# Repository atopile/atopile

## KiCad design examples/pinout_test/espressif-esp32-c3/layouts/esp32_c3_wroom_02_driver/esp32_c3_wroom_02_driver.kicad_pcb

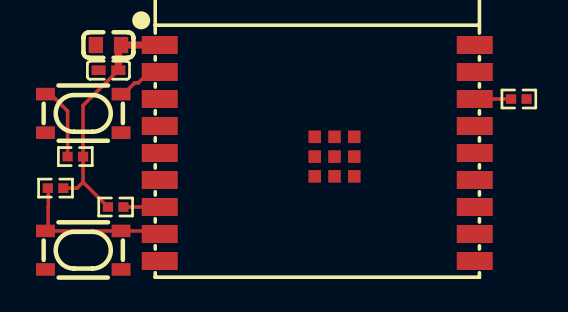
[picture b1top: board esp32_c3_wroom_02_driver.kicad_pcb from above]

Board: 2 copper layers, 9 parts (0 on the bottom side), 6 nets.

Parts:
C3: 22µF ±20% 6.3V X5R; C0603
C4: 100nF ±10% 16V X7R; C0402
R1, R2, R3: 10kΩ ±1% 62.5mW; R0402
R4: 5.1kΩ ±1% 62.5mW; R0402
SW1, SW2: KEY-SMD_4P-L4.2-W3.2-P2.20-LS4.6
U1: WIFIM-SMD_18P-L20.0-W18.0-P1.50

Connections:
GND: C3.2, C4.2, SW1.1, SW1.2, SW2.1, SW2.2, U1.9, U1.19
MISO: R2.1, U1.7
N_TRST: R3.2, SW2.3, SW2.4, U1.2
VCC: C3.1, C4.1, R1.2, R2.2, R3.1, R4.1, U1.1
data_1: R1.1, U1.16
output: R4.2, SW1.3, SW1.4, U1.8

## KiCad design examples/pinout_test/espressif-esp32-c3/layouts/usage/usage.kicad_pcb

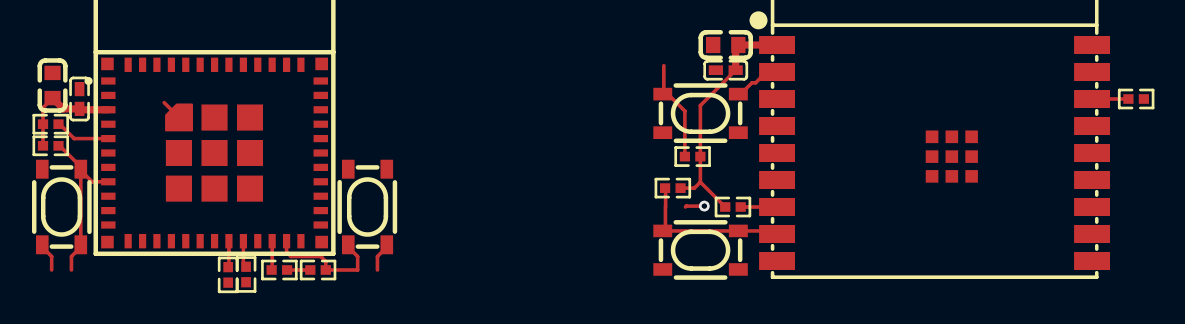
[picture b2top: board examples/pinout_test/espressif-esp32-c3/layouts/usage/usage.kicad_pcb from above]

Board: 2 copper layers, 20 parts (0 on the bottom side), 16 nets.

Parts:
C2, C6: 22µF ±20% 6.3V X5R; C0603
C3, C7: 100nF ±10% 16V X7R; C0402
R1, R2, R4, R5, R6, R7, R8, R10: 10kΩ ±1% 62.5mW; R0402
R3, R9: 5.1kΩ ±1% 62.5mW; R0402
SW1, SW2, SW3, SW4: KEY-SMD_4P-L4.2-W3.2-P2.20-LS4.6
U1: WIFIM-SMD_ESP32-C3-MINI-1
U2: WIFIM-SMD_18P-L20.0-W18.0-P1.50

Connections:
GND: C2.2, C3.2, C6.2, C7.2, SW1.1, SW1.2, SW2.1, SW2.2, SW3.1, SW3.2, SW4.1, SW4.2, U1.1, U1.2, U1.11, U1.14, U1.36, U1.37, U1.38, U1.39, U1.40, U1.41, U1.42, U1.43, U1.44, U1.45, U1.46, U1.47, U1.48, U1.49, U1.50, U1.51, U1.52, U1.53, U2.9, U2.19
MISO: R2.1, R8.1, U1.22, U2.7
MOSI: U1.21, U2.6
SCK: U1.12, U2.18
SCL: R6.2, U1.20, U2.5
SCLK: U1.16, U2.10
SD: U1.13, U2.17
SDA: R5.2, U1.19, U2.4
VCC: C2.1, C3.1, C6.1, C7.1, R1.2, R2.2, R3.1, R4.1, R5.1, R6.1, R7.2, R8.2, R9.1, R10.1, U1.3, U2.1
WS: U1.6, U2.15
mini_module-gpio[9]-output: R3.2, SW1.3, SW1.4, U1.23
mini_module-jtag-N_TRST: R4.2, SW2.3, SW2.4, U1.8
mini_module-mspi[2]-data_1: R1.1, U1.5
wroom_module-gpio[9]-output: R9.2, SW3.3, SW3.4, U2.8
wroom_module-jtag-N_TRST: R10.2, SW4.3, SW4.4, U2.2
wroom_module-mspi[2]-data_1: R7.1, U2.16

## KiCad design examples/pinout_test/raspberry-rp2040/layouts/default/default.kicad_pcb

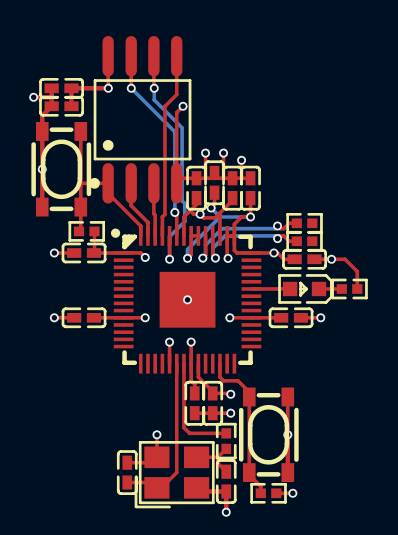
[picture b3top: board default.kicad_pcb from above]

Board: 4 copper layers, 26 parts (0 on the bottom side), 17 nets.

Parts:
C2, C8, C15: 2.2µF ±20% 6.3V X5R; C0402
C3, C4, C9, C10, C11, C12, C13, C14, C16: 100nF ±10% 16V X7R; C0402
C5, C6: 15pF ±5% 50V C0G; C0402
LED1: LED0603-RD
R1, R3, R4: 10kΩ ±1% 62.5mW; R0402
R2: 1kΩ ±1% 62.5mW; R0402
R5, R6: 27Ω ±1% 62.5mW; R0402
SW1, SW2: KEY-SMD_4P-L4.2-W3.2-P2.20-LS4.6
U1: LQFN-56_L7.0-W7.0-P0.4-EP
U2: SOIC-8_L5.3-W5.3-P1.27-LS8.0-BL
X1: CRYSTAL-SMD_4P-L3.2-W2.5-BL

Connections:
A: LED1.2, U1.37
GND: C2.2, C3.2, C4.2, C5.2, C6.2, C8.2, C9.2, C10.2, C11.2, C12.2, C13.2, C14.2, C15.2, C16.2, R3.1, SW1.3, SW1.4, SW2.3, SW2.4, U1.19, U1.57, U2.4, X1.2, X1.4
K: LED1.1, R3.2
RUN: R4.1, SW2.1, SW2.2, U1.26
XIN: C5.1, U1.20, X1.1
XOUT: R2.2, U1.21
_core_regulator_out_power-VCC: C2.1, C3.1, C4.1, U1.23, U1.45, U1.50
chip_select: R1.1, SW1.1, SW1.2, U1.56, U2.1
clock: U1.52, U2.6
data_0: U1.53, U2.5
data_1: U1.55, U2.2
data_2: U1.54, U2.3
data_3: U1.51, U2.7
output: C6.1, R2.1, X1.3
output-USB_D_N: R6.2, U1.46
output-USB_D_P: R5.2, U1.47
power-VCC: C8.1, C9.1, C10.1, C11.1, C12.1, C13.1, C14.1, C15.1, C16.1, R1.2, R4.2, U1.1, U1.10, U1.22, U1.33, U1.42, U1.43, U1.44, U1.48, U1.49, U2.8

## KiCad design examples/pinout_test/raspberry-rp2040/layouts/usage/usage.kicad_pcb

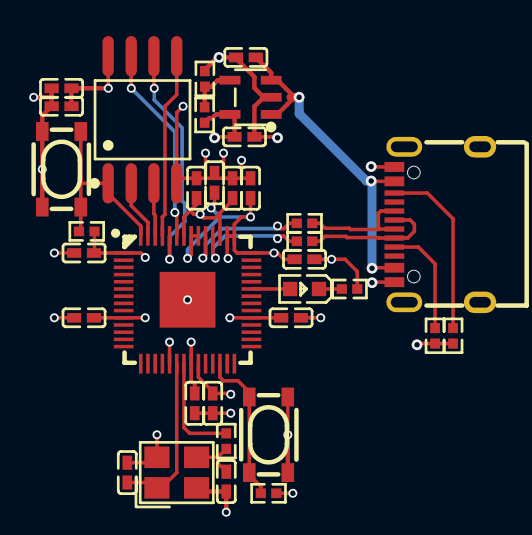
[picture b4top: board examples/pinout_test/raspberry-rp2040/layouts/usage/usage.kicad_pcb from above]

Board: 4 copper layers, 34 parts (0 on the bottom side), 23 nets.

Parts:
C1, C2: 1µF ±10% 25V X5R; C0402
C4, C9, C16: 2.2µF ±20% 6.3V X5R; C0402
C5, C6, C10, C11, C12, C13, C14, C15, C17: 100nF ±10% 16V X7R; C0402
C7, C8: 15pF ±5% 50V C0G; C0402
LED1: LED0603-RD
R1, R3, R5, R6: 10kΩ ±1% 62.5mW; R0402
R2: 20kΩ ±1% 62.5mW; R0402
R4: 1kΩ ±1% 62.5mW; R0402
R7, R8: 27Ω ±1% 62.5mW; R0402
R9, R10: 51kΩ ±1% 62.5mW; R0402
SW1, SW2: KEY-SMD_4P-L4.2-W3.2-P2.20-LS4.6
U1: SOT-23-5_L3.0-W1.7-P0.95-LS2.8-BL
U2: LQFN-56_L7.0-W7.0-P0.4-EP
U3: SOIC-8_L5.3-W5.3-P1.27-LS8.0-BL
USB1: USB-C-SMD_TYPE-C-6PIN-2MD-073
X1: CRYSTAL-SMD_4P-L3.2-W2.5-BL

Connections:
A: LED1.2, U2.37
CC1: R9.2, USB1.4
CC2: R10.2, USB1.10
GND: C1.2, C2.2, C4.2, C5.2, C6.2, C7.2, C8.2, C9.2, C10.2, C11.2, C12.2, C13.2, C14.2, C15.2, C16.2, C17.2, R1.2, R5.1, R9.1, R10.1, SW1.3, SW1.4, SW2.3, SW2.4, U1.2, U2.19, U2.57, U3.4, USB1.1, USB1.12, USB1.13, USB1.14, X1.2, X1.4
K: LED1.1, R5.2
RUN: R6.1, SW2.1, SW2.2, U2.26
VDIV_OUTPUT: R1.1, R2.2, U1.4
XIN: C7.1, U2.20, X1.1
XOUT: R4.2, U2.21
_core_regulator_out_power-VCC: C4.1, C5.1, C6.1, U2.23, U2.45, U2.50
chip_select: R3.1, SW1.1, SW1.2, U2.56, U3.1
clock: U2.52, U3.6
data_0: U2.53, U3.5
data_1: U2.55, U3.2
data_2: U2.54, U3.3
data_3: U2.51, U3.7
input-USB_D_N: R8.1, USB1.5, USB1.7
input-USB_D_P: R7.1, USB1.6, USB1.8
output: C8.1, R4.1, X1.3
output-USB_D_N: R8.2, U2.46
output-USB_D_P: R7.2, U2.47
power-VCC: C2.1, C9.1, C10.1, C11.1, C12.1, C13.1, C14.1, C15.1, C16.1, C17.1, R2.1, R3.2, R6.2, U1.5, U2.1, U2.10, U2.22, U2.33, U2.42, U2.43, U2.44, U2.48, U2.49, U3.8
power_in-VCC: C1.1, U1.1, U1.3, USB1.2, USB1.11

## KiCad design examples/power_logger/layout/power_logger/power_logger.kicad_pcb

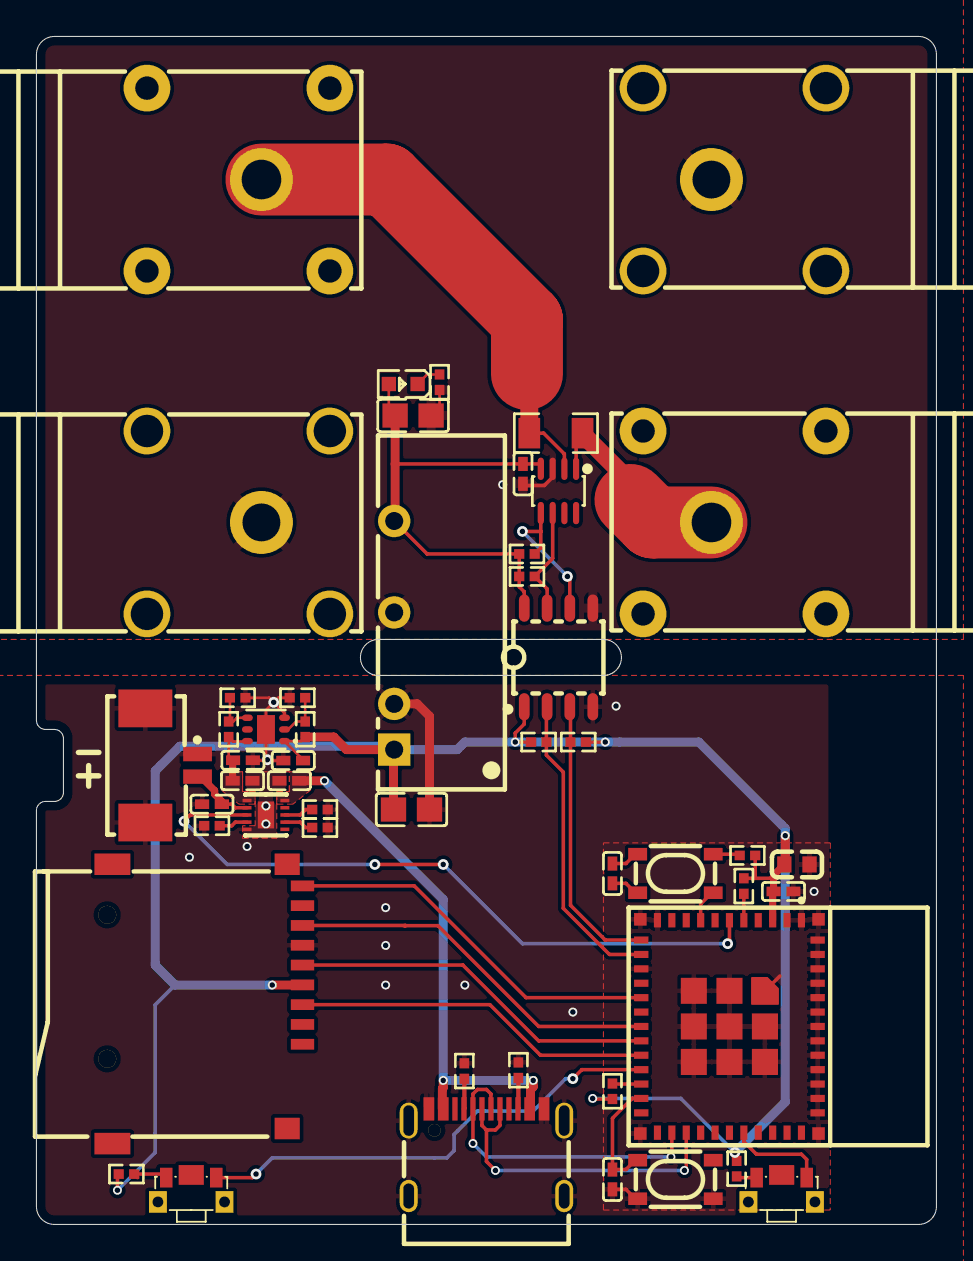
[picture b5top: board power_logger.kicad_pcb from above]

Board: 2 copper layers, 50.0 x 66.0 mm, 51 parts (1 on the bottom side), 38 nets.

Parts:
B1: EEMB_BATTERY_LP402535
C1, C3, C5, C6: 1µF ±10% 25V X5R; C0402
C2: 10µF ±20% 6.3V X5R; C0402
C4, C7, C8, C12: 100nF ±10% 16V X7R; C0402
C9: 22µF ±20% 6.3V X5R; C0603
C10: 2.2µF ±10% 25V X7R; C0805
C11: 10µF ±10% 25V X5R; C0805
Card1: TF-SMD_TF-01A
D1: LED0603-RD
J1, J3: ANT-TH_L33.0-W12.0_BLACK
J2, J4: ANT-TH_L33.0-W12.0_RED
R1, R2, R4, R5, R10, R11, R12, R13, R14, R15, R19, R20: 10kΩ ±1% 62.5mW; R0402
R3, R7: 100kΩ ±1% 62.5mW; R0402
R6: 25mΩ ±1% 1W; R1206
R8: 150kΩ ±1% 62.5mW; R0402
R9, R18: 2kΩ ±1% 62.5mW; R0402
R16, R17: 4.7kΩ ±1% 62.5mW; R0402
SW1, SW2: KEY-SMD_SKTDLDE010
SW3, SW4: KEY-SMD_4P-L4.2-W3.2-P2.20-LS4.6
U1: WSON-10_L2.2-W2.0-P0.40-BL-EP_TI_DLH0010A
U2: SOT-23-8_L2.9-W1.6-P0.65-LS2.8-BR
U3: WSON-6_L2.0-W2.0-P0.65-TL-EP
U4: WIFIM-SMD_ESP32-C3-MINI-1
U5: PWRM-TH_BXXXXS-2WR3
U6: SOIC-8_L4.9-W3.9-P1.27-LS6.0-TL
U7: CONN-SMD_532610271
USB1: USB-C-SMD_KH-TYPE-C-16P

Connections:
A5: R16.1, USB1.A5
B5: R17.1, USB1.B5
CD: Card1.9, U4.16
EN: R7.1, R8.2, U3.4
FB: R9.1, R10.2, U3.2
GND: Card1.10, Card1.11, Card1.12, Card1.13
ILIM_VSET: R3.1, U1.7
INneg: J4.5, R6.2, U2.2
INpos: J2.5, R6.1, U2.1
ISET: R1.1, U1.8
SCL2: R19.1, U2.5, U6.6
SDA2: R20.1, U2.6, U6.7
cathode: D1.1, R18.1
gnd: C1.2, C2.2, C3.2, C5.2, C6.2, C7.1, C9.2, C10.2, C12.2, Card1.6, R1.2, R2.2, R3.2, R7.2, R9.2, R16.2, R17.2, SW3.1, SW3.2, U1.5, U1.11, U3.3, U3.7, U4.1, U4.2, U4.11, U4.14, U4.36, U4.37, U4.38, U4.39, U4.40, U4.41, U4.42, U4.43, U4.44, U4.45, U4.46, U4.47, U4.48, U4.49, U4.50, U4.51, U4.52, U4.53, U5.2, U6.4, U7.1, U7.3, U7.4, USB1.1, USB1.2, USB1.3, USB1.4, USB1.A1, USB1.A12, USB1.B1, USB1.B12
gnd-1: C4.2, C11.2, J1.5, J3.5, R18.2, U2.3, U2.7, U5.4, U6.5
hv: C5.1, C9.1, C10.1, C12.1, Card1.4, R4.2, R5.2, R10.1, R11.2, R12.2, R13.2, R14.2, R15.2, U3.1, U4.3, U5.1, U6.1
hv-1: C4.1, C11.1, D1.2, R19.2, R20.2, U2.4, U5.6, U6.8
hv-2: C3.1, U1.10, USB1.A4, USB1.A9, USB1.B4, USB1.B9
hv-3: C1.1, U1.2, U7.2
hv-4: C2.1, C6.1, R8.1, U1.1, U3.6
input: C8.1, R13.1, SW4.1, SW4.2
input-1: R4.1, SW1.1
input-2: R5.1, SW2.1
line: R14.1, U4.12, U6.3
line-1: R15.1, U4.13, U6.2
line-2: R11.1, U4.5
line-3: U1.3, U4.6
line-4: Card1.7, U4.18
line-5: Card1.5, U4.19
line-6: U4.26, USB1.A7, USB1.B7
line-7: U4.27, USB1.A6, USB1.B6
line-9: Card1.3, U4.20
line-10: R12.1, U4.22
nCE: R2.1, U1.4
output: C8.2, SW4.3, SW4.4, U4.8
output-1: SW1.2, U4.31
output-2: SW2.2, U4.21
output-3: C7.2, SW3.3, SW3.4, U4.23
